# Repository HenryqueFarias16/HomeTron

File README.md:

# IOTs
projetos de automação residencial utilizando microcontrolador ESP12-E

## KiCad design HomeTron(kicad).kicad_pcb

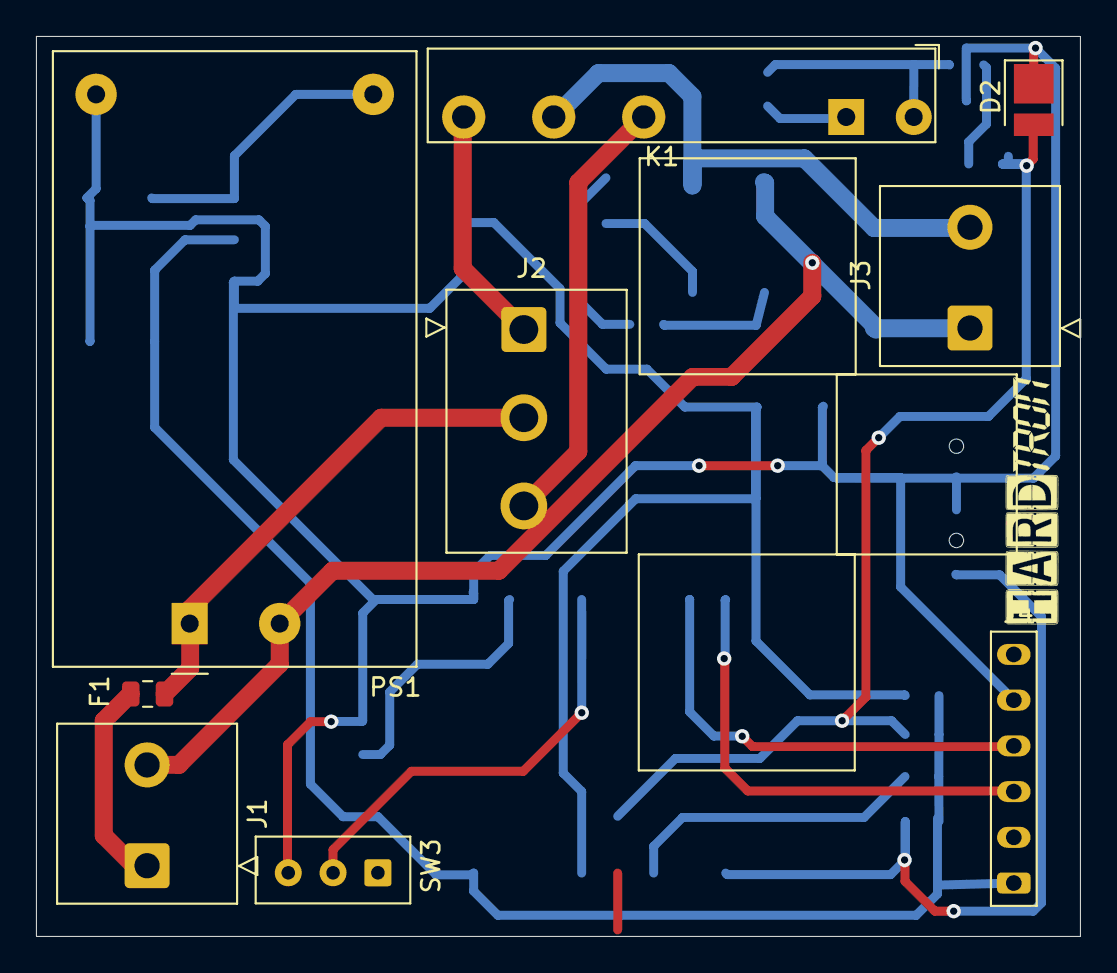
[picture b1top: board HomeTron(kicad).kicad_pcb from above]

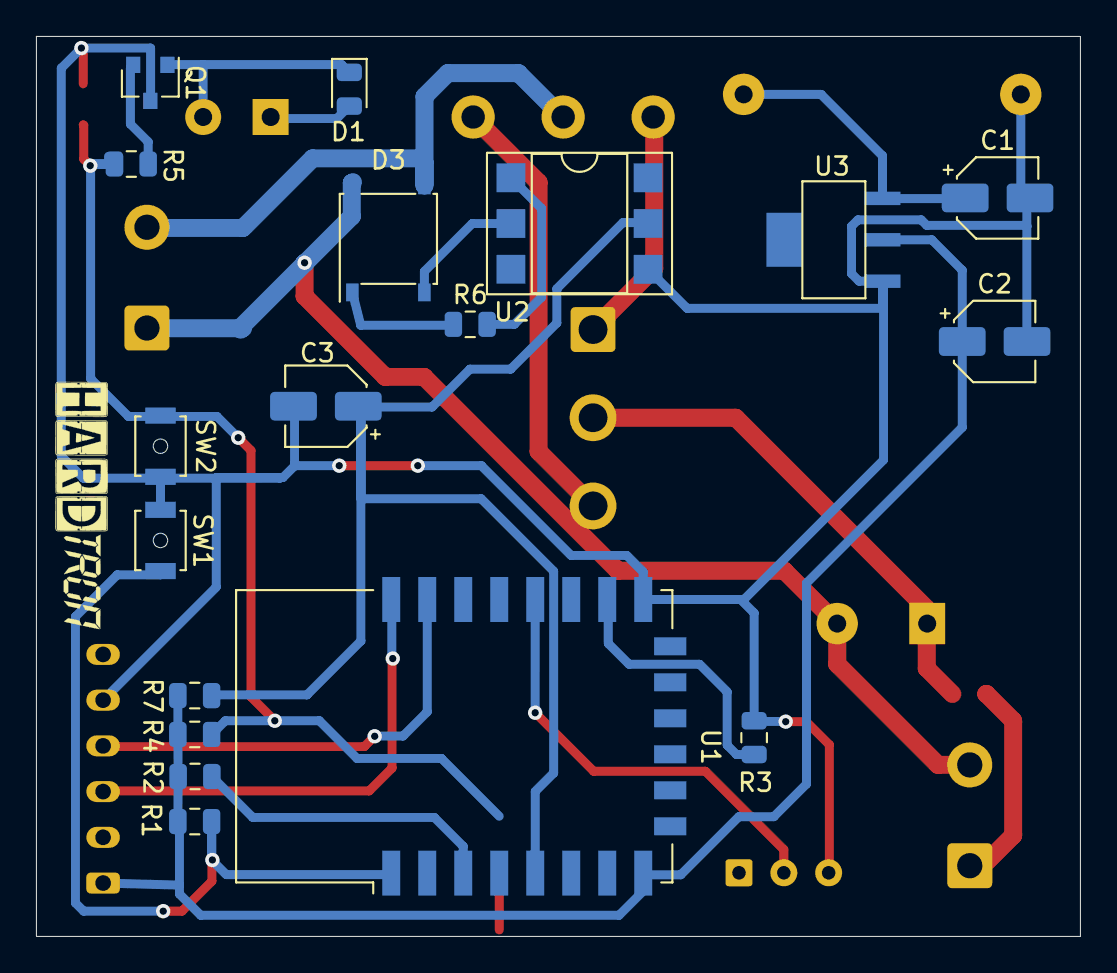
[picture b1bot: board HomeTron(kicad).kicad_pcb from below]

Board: 2 copper layers, 58.0 x 50.0 mm, 27 parts (18 on the bottom side), 23 nets.

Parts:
C1, C2: 10uF; CP_Elec_4x5.4
C3: 1uF; CP_Elec_4x5.4
D1: DIODE; D_0805_2012Metric
D2: LED; LED_PLCC_2835
D3: MBL110S; Diode_Bridge_Vishay_MBLS
F1: 1A; Fuse_0805_2012Metric
J1: InAC; Tblock10x10mm
J2: 300V/10A; Tblock3.10x10mm
J3: OutAC; Tblock10x10mm
J4: Cp2102; Wuerth_WR-WTB_64800611622_1x06_P2.50mm_Vertical
K1: FINDER-34.51; Relay_SPDT_Finder_34.51_Vertical
PS1: HLK-PM01; Converter_ACDC_HiLink_HLK-PMxx
Q1: BC547; SOT-23
R1, R2, R3, R4, R7: 10k; R_0805_2012Metric
R5: 1k; R_0805_2012Metric
R6: 300k; R_0805_2012Metric
SW1, SW2: B3U-1000P-B; SW_SPST_B3U-1000P-B
SW3: SS12D00; TE_826576-3_1x03_P1mm_Vertical
U1: ESP-12E
U2: 4N25; DIP-6_W7.62mm_SMDSocket_SmallPads
U3: LM1117-3.3; R-PDSO-G4

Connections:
+3V3: C2.1, J4.1, R1.2, R2.2, R4.2, R7.1, U1.8, U3.2
+5V: D1.2, K1.A1
C: D3.3, J3.2, K1.11
C-Interrruptor: F1.2, J2.2, PS1.1
EN: R2.1, U1.3
Fase: F1.1, J1.1
GND: C1.2, C2.2, C3.2, D2.1, J4.5, PS1.3, Q1.3, R3.1, SW1.2, SW2.2, SW3.3, U1.15, U2.4, U3.1
Gpio0: SW3.2, U1.18
Gpio14: C3.1, R7.2, U1.5, U2.5
Gpio15: R3.2, U1.16
Gpio16: D2.2, R4.1, R5.1, SW2.1, U1.4
Na: J2.1, K1.14
unnamed: C1.1, PS1.4, U3.3
unnamed: D1.1, K1.A2, Q1.1
unnamed: D3.1, R6.1
unnamed: D3.2, U2.2
unnamed: Q1.2, R5.2
unnamed: R6.2, U2.1
Neutro: D3.4, J1.2, J3.1, PS1.2
Nf: J2.3, K1.12
Rst: R1.1, SW1.1, U1.1
Rx: J4.4, U1.21
Tx: J4.3, U1.22

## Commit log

2020-10-30 Create Firmware
2020-10-30 Rename Firmware to Firmware.ino
